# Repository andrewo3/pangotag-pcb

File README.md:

# Pangotag PCB

KiCad 10 project for a GNSS and motion tracking tag for the white-bellied pangolin, built in the
Harvard Microrobotics Laboratory.

## V2

`Pangotag_PCB_LCSC_compat4.kicad_pcb` is the V2 tag: a 31.94 × 27.18 mm, 6-layer, 1.6 mm board with
80 parts on both sides, using parts that JLCPCB stocks.

- STM32U575 microcontroller (LQFP-64) and a 32 GB eMMC on the underside
- u-blox MAX-M10S GNSS module with a U.FL antenna connector
- BMI270 IMU, BMP581 pressure sensor, T117 temperature sensor and LTC2944 coulomb counter on one I2C bus
- Two TPS62840 buck converters for always-on 1.9 V and 3.3 V rails, fed from a 2-pin battery connector
- USB-C for USB and, with a Type-C debug accessory, SWD: two comparators on CC1 and CC2 and an AND
  gate switch a TMUX1511 that puts SWCLK, SWDIO, SWO and NRST on contacts USB 2.0 leaves unused

`Dongle.kicad_pcb` is a 4-layer adapter that connects an ST-Link to the tag's USB-C port in either
orientation, with a reset button.

## Files

| Path | Contents |
| --- | --- |
| `Pangotag_PCB.kicad_sch` and its `Power`, `Communication`, `LEDs` and `st-link_conn` sheets | Schematic |
| `Pangotag_PCB_LCSC_compat4.kicad_pcb` | V2 tag board |
| `Dongle.kicad_pcb` | ST-Link debug dongle |
| `Pangotag_PCB.kicad_pcb` | The tag and an earlier dongle on one sheet |
| `Pangotag_PCB_LCSC_compat*.kicad_pcb`, `Only_Tag*.kicad_pcb` | Intermediate revisions |
| `jlcpcb/` | JLCPCB Gerber, BOM and placement files |
| `export_footprints.pretty/`, `FBGA153.pretty/`, `*.kicad_sym` | Project footprint and symbol libraries |
| `tag_render*.png` | Renders of the board and an enclosure model |

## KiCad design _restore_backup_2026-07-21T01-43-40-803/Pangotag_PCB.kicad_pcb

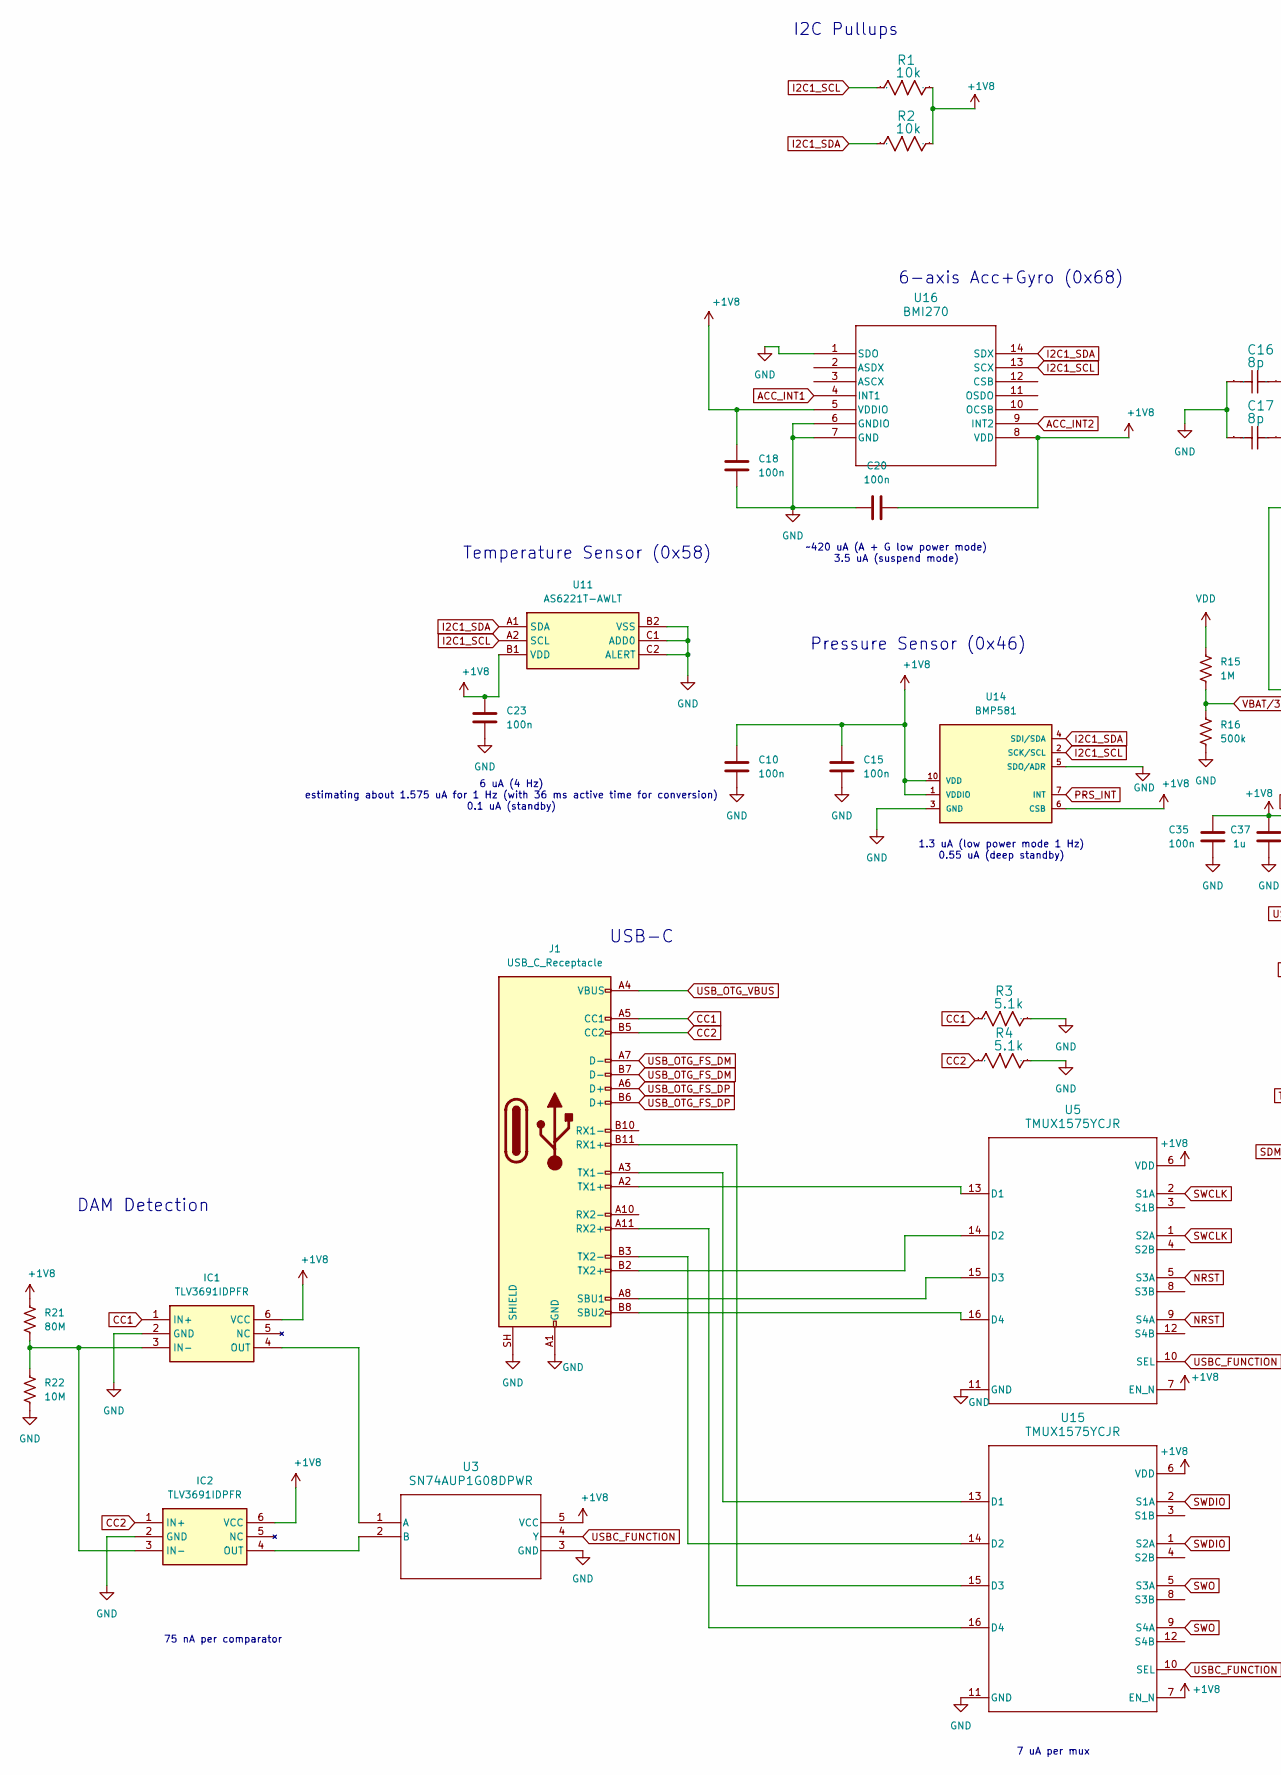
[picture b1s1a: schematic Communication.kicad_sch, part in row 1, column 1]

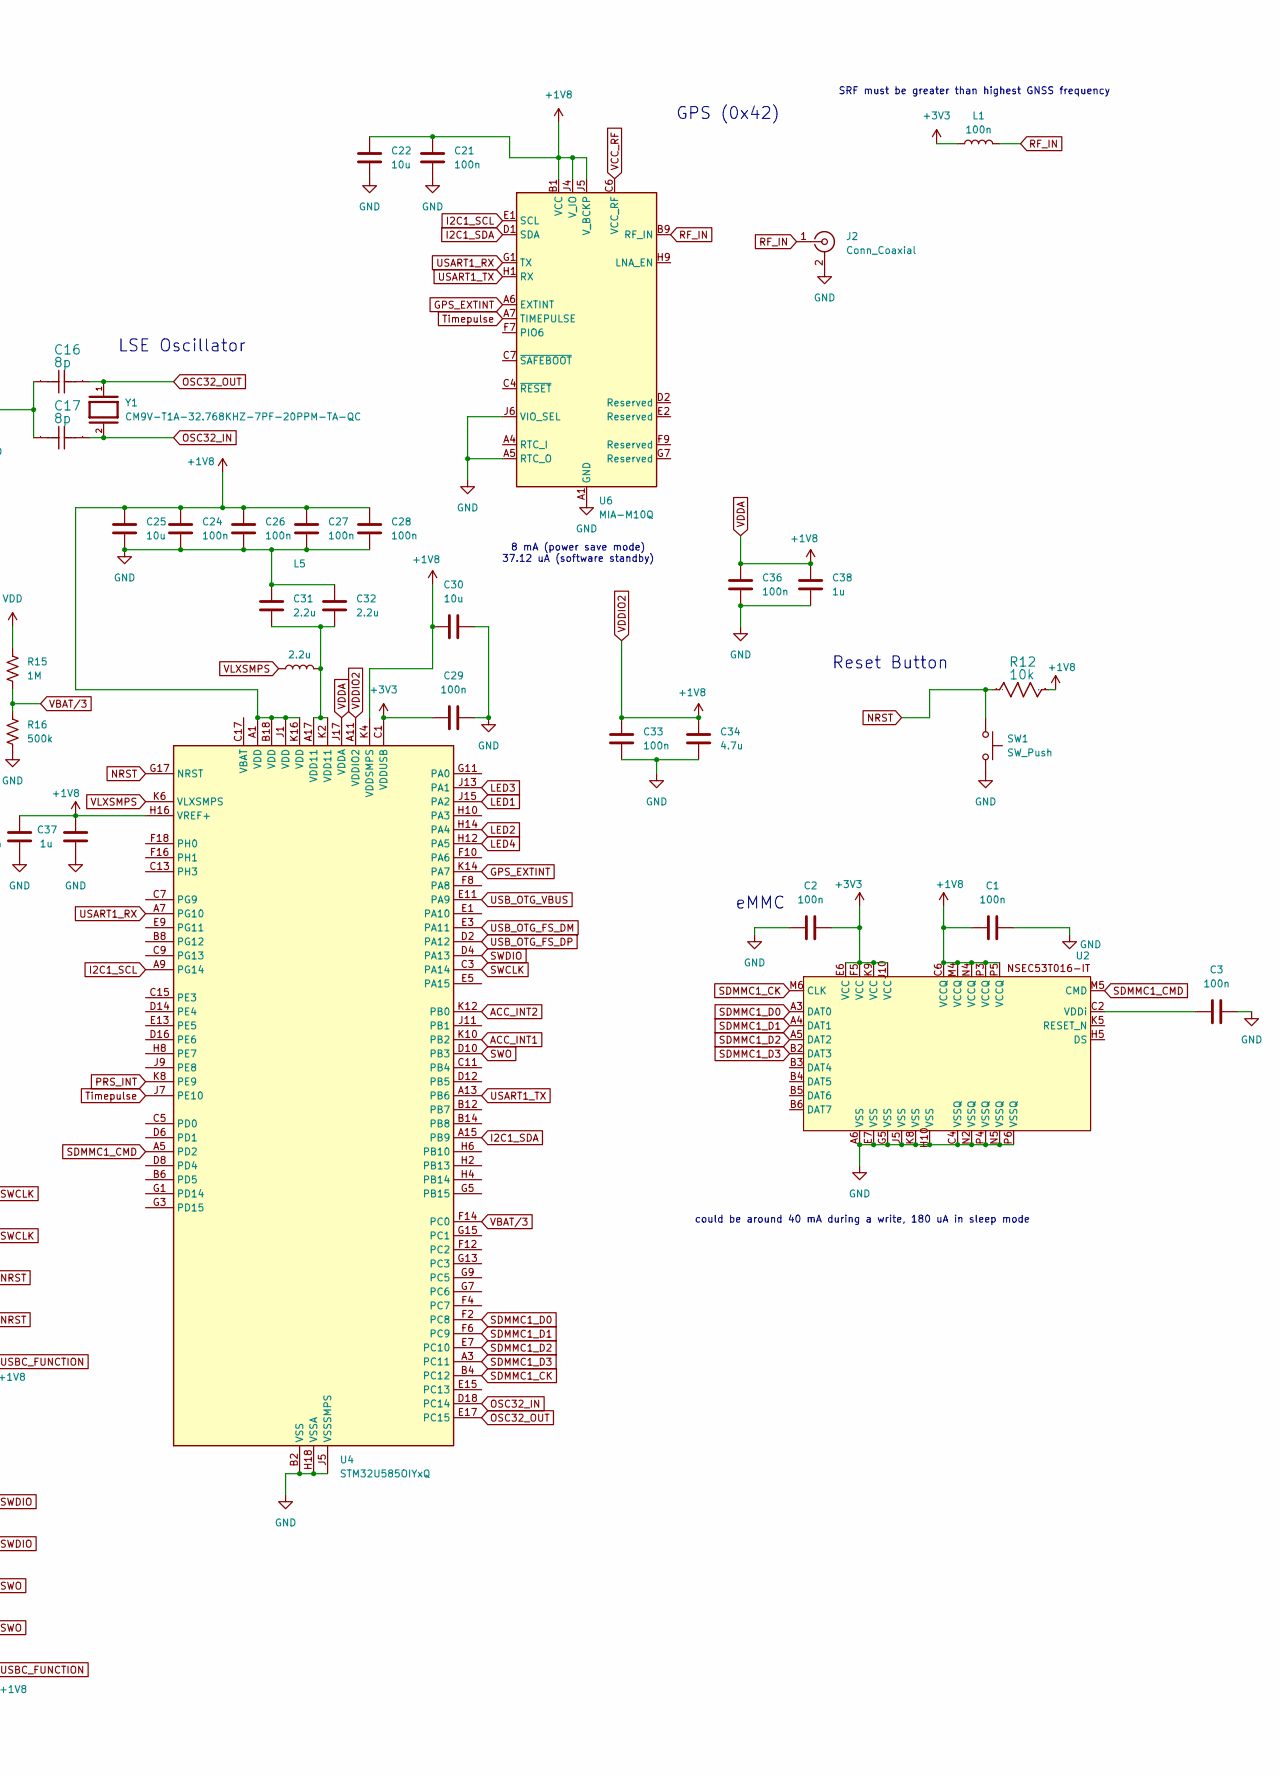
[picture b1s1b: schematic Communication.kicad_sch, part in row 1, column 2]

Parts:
C1, C2, C3, C10, C15, C18, C20, C21, C23, C24, C26, C27, C28, C29, C33, C35, C36: 100n; C_0201_0603Metric
C16, C17: 8p; C_0201_0603Metric
C22, C25, C30: 10u; C_0201_0603Metric
C31, C32: 2.2u; C_0201_0603Metric
C34: 4.7u; C_0201_0603Metric
C37, C38: 1u; C_0201_0603Metric
IC1, IC2: TLV3691IDPFR; Manufacturer_Part_Number TLV3691IDPFR; Mouser Part Number 595-TLV3691IDPFR
J1: USB_C_Receptacle; USB_C_Receptacle_Amphenol_12401610E4-2A_CircularHoles
J2: Conn_Coaxial; U.FL_Hirose_U.FL-R-SMT-1_Vertical
L1: 100n; L_0201_0603Metric
L5: 2.2u; L_0201_0603Metric
R1, R2, R12: 10k; R_0201_0603Metric
R3, R4: 5.1k; R_0201_0603Metric
R15: 1M; R_0201_0603Metric
R16: 500k; R_0201_0603Metric
R21: 80M; R_0201_0603Metric
R22: 10M; R_0201_0603Metric
SW1: SW_Push; SW_SPST_B3U-1000P
U2: BGA153N50P14X14_1150X1300X80
U3: SN74AUP1G08DPWR; DPW0005A_TEX
U4: STM32U585OIYxQ; ST_WLCSP-90_4.2x3.95mm_Layout18x10_P0.4mm_Stagger
U5, U15: TMUX1575YCJR; PREYCJ0016-IPC_A
U6: MIA-M10Q; ublox_LGA-53_4.5x4.5mm_Layout9x9_P0.5mm
U11: AS6221T-AWLT; BGA6C40P2X3_102X150X52; Manufacturer_Part_Number AS6221T-AWLT; Mouser Part Number 985-AS6221T-AWLT
U14: BMP581
U16: BMI270; BMI270_BOS
Y1: CM9V-T1A-32.768KHZ-7PF-20PPM-TA-QC; XTAL_CM9V-T1A-32.768KHZ-7PF-20PPM-TA-QC; PARTREV 8.2/07.2022

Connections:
+3V3: C2.2, C29.2, L1.1, U2.E6 (VCC), U2.F5 (VCC), U2.J10 (VCC), U2.K9 (VCC), U4.C1 (VDDUSB); also elsewhere on the board
ACC_INT1: U4.K10 (PB2), U16.4 (INT1)
ACC_INT2: U4.K12 (PB0), U16.9 (INT2)
CC1: IC1.1 (IN+), J1.A5 (CC1), R3.1
CC2: IC2.1 (IN+), J1.B5 (CC2), R4.1
GND: C1.2, C2.1, C3.2, C10.2, C15.2, C16.1, C17.1, C18.2, C20.1, C21.2, C22.2, C23.2, C24.1, C25.1, C26.1, C27.1, C28.1, C29.1, C30.1, C31.2, C32.2, C33.1, C34.1, C35.1, C36.1, C37.1, C38.1, IC1.2 (GND), IC2.2 (GND), J1.A1 (GND), J1.A12 (GND), J1.B1 (GND), J1.B12 (GND), J1.SH (SHIELD), J2.2 (Ext), R3.2, R4.2, R16.2, R22.2, SW1.2, U2.A6 (VSS), U2.C4 (VSSQ), U2.E7 (VSS), U2.G5 (VSS), U2.H10 (VSS), U2.J5 (VSS), U2.K8 (VSS), U2.N2 (VSSQ), U2.N5 (VSSQ), U2.P4 (VSSQ), U2.P6 (VSSQ), U3.3 (GND), U4.B2 (VSS), U4.B10 (VSS), U4.B16 (VSS), U4.H18 (VSSA), U4.J3 (VSS), U4.J5 (VSSSMPS), U4.K18 (VSS), U5.11 (GND), U6.A1 (GND), U6.A2 (GND), U6.A3 (GND), U6.A5 (RTC_O), U6.A8 (GND), U6.A9 (GND), U6.B2 (GND), U6.B8 (GND), U6.C3 (GND), U6.C9 (GND), U6.E3 (GND), U6.E4 (GND), U6.E9 (GND), U6.F1 (GND), U6.F3 (GND), U6.F4 (GND), U6.G3 (GND), U6.G4 (GND), U6.G5 (GND), U6.G6 (GND), U6.H8 (GND), U6.J6 (VIO_SEL), U6.J8 (GND), U6.J9 (GND), U11.B2 (VSS), U11.C1 (ADD0), U11.C2 (ALERT), U14.3 (GND), U14.5 (SDO/ADR), U14.8 (GND), U14.9 (GND), U15.11 (GND), U16.1 (SDO), U16.6 (GNDIO), U16.7 (GND); also elsewhere on the board
GPS_EXTINT: U4.K14 (PA7), U6.A6 (EXTINT)
I2C1_SCL: R1.1, U4.A9 (PG14), U6.E1 (SCL), U11.A2 (SCL), U14.2 (SCK/SCL), U16.13 (SCX); also elsewhere on the board
I2C1_SDA: R2.1, U4.A15 (PB9), U6.D1 (SDA), U11.A1 (SDA), U14.4 (SDI/SDA), U16.14 (SDX); also elsewhere on the board
LED1: U4.J15 (PA2); also elsewhere on the board
LED2: U4.H14 (PA4); also elsewhere on the board
LED3: U4.J13 (PA1); also elsewhere on the board
LED4: U4.H12 (PA5); also elsewhere on the board
NRST: R12.2, SW1.1, U4.G17 (NRST), U5.5 (S3A), U5.9 (S4A)
unnamed: C31.1, C32.1, L5.2, U4.A17 (VDD11), U4.K2 (VDD11)
unnamed: IC1.3 (IN-), IC2.3 (IN-), R21.2, R22.1
unnamed: IC1.4 (OUT), U3.1 (A)
unnamed: IC2.4 (OUT), U3.2 (B)
unnamed: J1.B11 (RX1+), U15.15 (D3)
unnamed: J1.A11 (RX2+), U15.16 (D4)
unnamed: J1.A8 (SBU1), U5.15 (D3)
unnamed: J1.B8 (SBU2), U5.16 (D4)
unnamed: J1.A2 (TX1+), U5.13 (D1)
unnamed: J1.A3 (TX1-), U15.13 (D1)
unnamed: J1.B2 (TX2+), U5.14 (D2)
unnamed: J1.B3 (TX2-), U15.14 (D2)
unnamed: C3.1, U2.C2 (VDDi)
OSC32_IN: C17.2, U4.D18 (PC14), Y1.2
OSC32_OUT: C16.2, U4.E17 (PC15), Y1.1
PRS_INT: U4.K8 (PE9), U14.7 (INT)
RF_IN: J2.1 (In), L1.2, U6.B9 (RF_IN)
SDMMC1_CK: U2.M6 (CLK), U4.B4 (PC12)
SDMMC1_CMD: U2.M5 (CMD), U4.A5 (PD2)
SDMMC1_D0: U2.A3 (DAT0), U4.F2 (PC8)
SDMMC1_D1: U2.A4 (DAT1), U4.F6 (PC9)
SDMMC1_D2: U2.A5 (DAT2), U4.E7 (PC10)
SDMMC1_D3: U2.B2 (DAT3), U4.A3 (PC11)
SWCLK: U4.C3 (PA14), U5.1 (S2A), U5.2 (S1A)
SWDIO: U4.D4 (PA13), U15.1 (S2A), U15.2 (S1A)
SWO: U4.D10 (PB3), U15.5 (S3A), U15.9 (S4A)
Timepulse: U4.J7 (PE10), U6.A7 (TIMEPULSE)
USART1_RX: U4.A7 (PG10), U6.G1 (TX)
USART1_TX: U4.A13 (PB6), U6.H1 (RX)
USBC_FUNCTION: U3.4 (Y), U5.10 (SEL), U15.10 (SEL)
USB_OTG_FS_DM: J1.A7 (D-), J1.B7 (D-), U4.E3 (PA11)
USB_OTG_FS_DP: J1.A6 (D+), J1.B6 (D+), U4.D2 (PA12)
USB_OTG_VBUS: J1.A4 (VBUS), J1.A9 (VBUS), J1.B4 (VBUS), J1.B9 (VBUS), U4.E11 (PA9)
VBAT/3: R15.2, R16.1, U4.F14 (PC0)
VCC_RF: U6.C6 (VCC_RF)
VDD: R15.1; also elsewhere on the board
VDDA: C1.1, C10.1, C15.1, C18.1, C20.2, C21.1, C22.1, C23.1, C24.2, C25.2, C26.2, C27.2, C28.2, C30.2, C33.2, C34.2, C35.2, C36.2, C37.2, C38.2, IC1.6 (VCC), IC2.6 (VCC), R1.2, R2.2, R12.1, R21.1, U2.C6 (VCCQ), U2.M4 (VCCQ), U2.N4 (VCCQ), U2.P3 (VCCQ), U2.P5 (VCCQ), U3.5 (VCC), U4.A1 (VDD), U4.A11 (VDDIO2), U4.B18 (VDD), U4.H16 (VREF+), U4.J1 (VDD), U4.J17 (VDDA), U4.K4 (VDDSMPS), U4.K16 (VDD), U5.6 (VDD), U5.7 (EN_N), U6.B1 (VCC), U6.J4 (V_IO), U6.J5 (V_BCKP), U11.B1 (VDD), U14.1 (VDDIO), U14.6 (CSB), U14.10 (VDD), U15.6 (VDD), U15.7 (EN_N), U16.5 (VDDIO), U16.8 (VDD); also elsewhere on the board
VLXSMPS: L5.1, U4.K6 (VLXSMPS)

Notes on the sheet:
Temperature Sensor (0x58)
GPS (0x42)
75 nA per comparator
I2C Pullups
SRF must be greater than highest GNSS frequency
Reset Button
8 mA (power save mode) 37.12 uA (software standby)
could be around 40 mA during a write, 180 uA in sleep mode
6-axis Acc+Gyro (0x68)
DAM Detection
eMMC
6 uA (4 Hz) estimating about 1.575 uA for 1 Hz (with 36 ms active time for conversion) 0.1 uA (standby)
7 uA per mux
1.3 uA (low power mode 1 Hz) 0.55 uA (deep standby)
LSE Oscillator
Pressure Sensor (0x46)
~420 uA (A + G low power mode) 3.5 uA (suspend mode)
USB-C

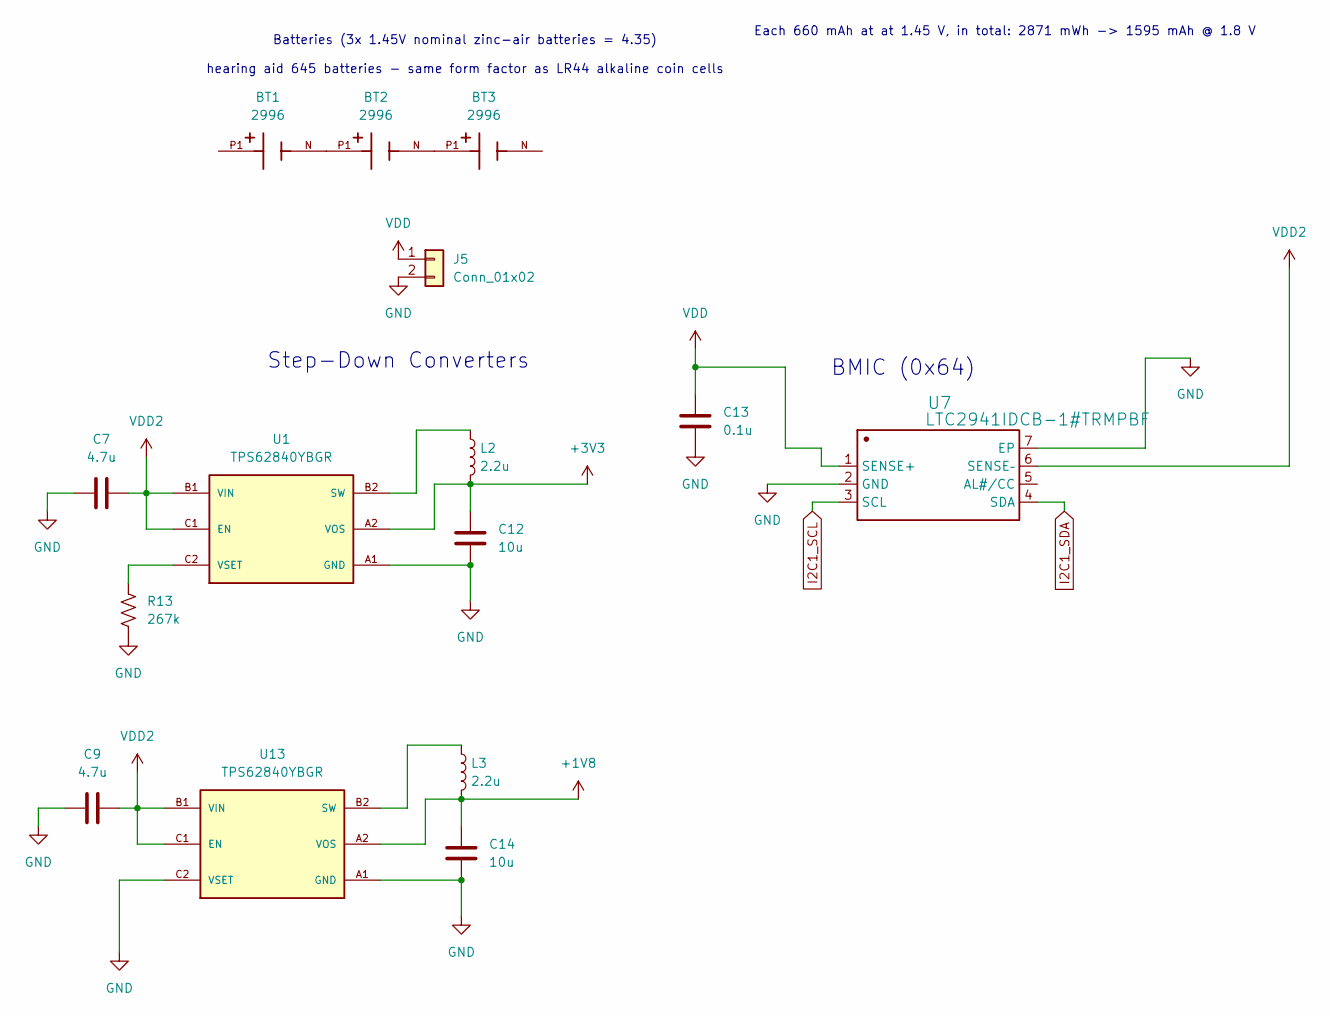
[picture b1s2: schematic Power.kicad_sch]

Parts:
BT1, BT2, BT3: 2996; BAT_2996; PARTREV F
C7, C9: 4.7u; C_0201_0603Metric
C12, C14: 10u; C_0201_0603Metric
C13: 0.1u; C_0201_0603Metric
J5: Conn_01x02; Hirose_DF57H-2P-1.2V_1x02_P1.2mm_Socket
L2, L3: 2.2u; L_0201_0603Metric
R13: 267k; R_0201_0603Metric
U1, U13: TPS62840YBGR; BGA6N40P3X2_146X96X50N; PARTREV D
U7: LTC2941IDCB-1#TRMPBF; DFN-6-1EP_3x2mm_P0.5mm_EP1.65x1.35mm; Manufacturer Part LTC2941IDCB-1#TRMPBF

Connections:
+3V3: C12.1, L2.2, U1.A2 (VOS); also elsewhere on the board
GND: C7.2, C9.2, C12.2, C13.2, C14.2, J5.2, R13.2, U1.A1 (GND), U7.2 (GND), U7.7 (EP), U13.A1 (GND), U13.C2 (VSET); also elsewhere on the board
I2C1_SCL: U7.3 (SCL); also elsewhere on the board
I2C1_SDA: U7.4 (SDA); also elsewhere on the board
unnamed: BT1.N, BT2.P1, BT2.P2
unnamed: BT1.P1, BT1.P2
unnamed: BT2.N, BT3.P1, BT3.P2
unnamed: L2.1, U1.B2 (SW)
unnamed: R13.1, U1.C2 (VSET)
unnamed: L3.1, U13.B2 (SW)
VDD: C13.1, J5.1, U7.1 (SENSE+); also elsewhere on the board
VDD2: C7.1, C9.1, U1.B1 (VIN), U1.C1 (EN), U7.6 (SENSE–), U13.B1 (VIN), U13.C1 (EN)
VDDA: C14.1, L3.2, U13.A2 (VOS); also elsewhere on the board

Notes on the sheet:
Each 660 mAh at at 1.45 V, in total: 2871 mWh -> 1595 mAh @ 1.8 V
BMIC (0x64)
Batteries (3x 1.45V nominal zinc-air batteries = 4.35) hearing aid 645 batteries - same form factor as LR44 alkaline coin cells
Step-Down Converters

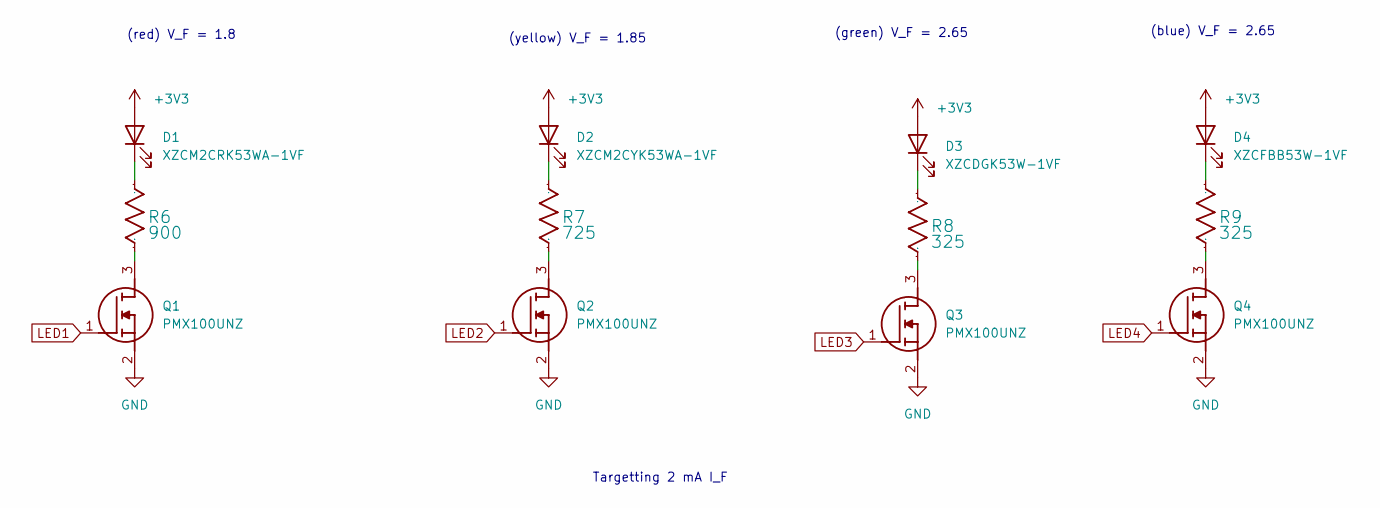
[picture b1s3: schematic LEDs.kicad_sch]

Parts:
D1: XZCM2CRK53WA-1VF; LED_0201_0603Metric
D2: XZCM2CYK53WA-1VF; LED_0201_0603Metric
D3: XZCDGK53W-1VF; LED_0201_0603Metric
D4: XZCFBB53W-1VF; LED_0201_0603Metric
Q1, Q2, Q3, Q4: PMX100UNZ; Manufacturer_Part_Number PMX100UNZ; Mouser Part Number 771-PMX100UNZ
R6: 900; R_0201_0603Metric
R7: 725; R_0201_0603Metric
R8, R9: 325; R_0201_0603Metric

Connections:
+3V3: D1.2 (A), D2.2 (A), D3.2 (A), D4.2 (A); also elsewhere on the board
GND: Q1.2 (S), Q2.2 (S), Q3.2 (S), Q4.2 (S); also elsewhere on the board
LED1: Q1.1 (G); also elsewhere on the board
LED2: Q2.1 (G); also elsewhere on the board
LED3: Q3.1 (G); also elsewhere on the board
LED4: Q4.1 (G); also elsewhere on the board
unnamed: D1.1 (K), R6.2
unnamed: D2.1 (K), R7.2
unnamed: D3.1 (K), R8.2
unnamed: D4.1 (K), R9.2
unnamed: Q1.3 (D), R6.1
unnamed: Q2.3 (D), R7.1
unnamed: Q3.3 (D), R8.1
unnamed: Q4.3 (D), R9.1

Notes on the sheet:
(blue) V_F = 2.65
(yellow) V_F = 1.85
(red) V_F = 1.8
(green) V_F = 2.65
Targetting 2 mA I_F

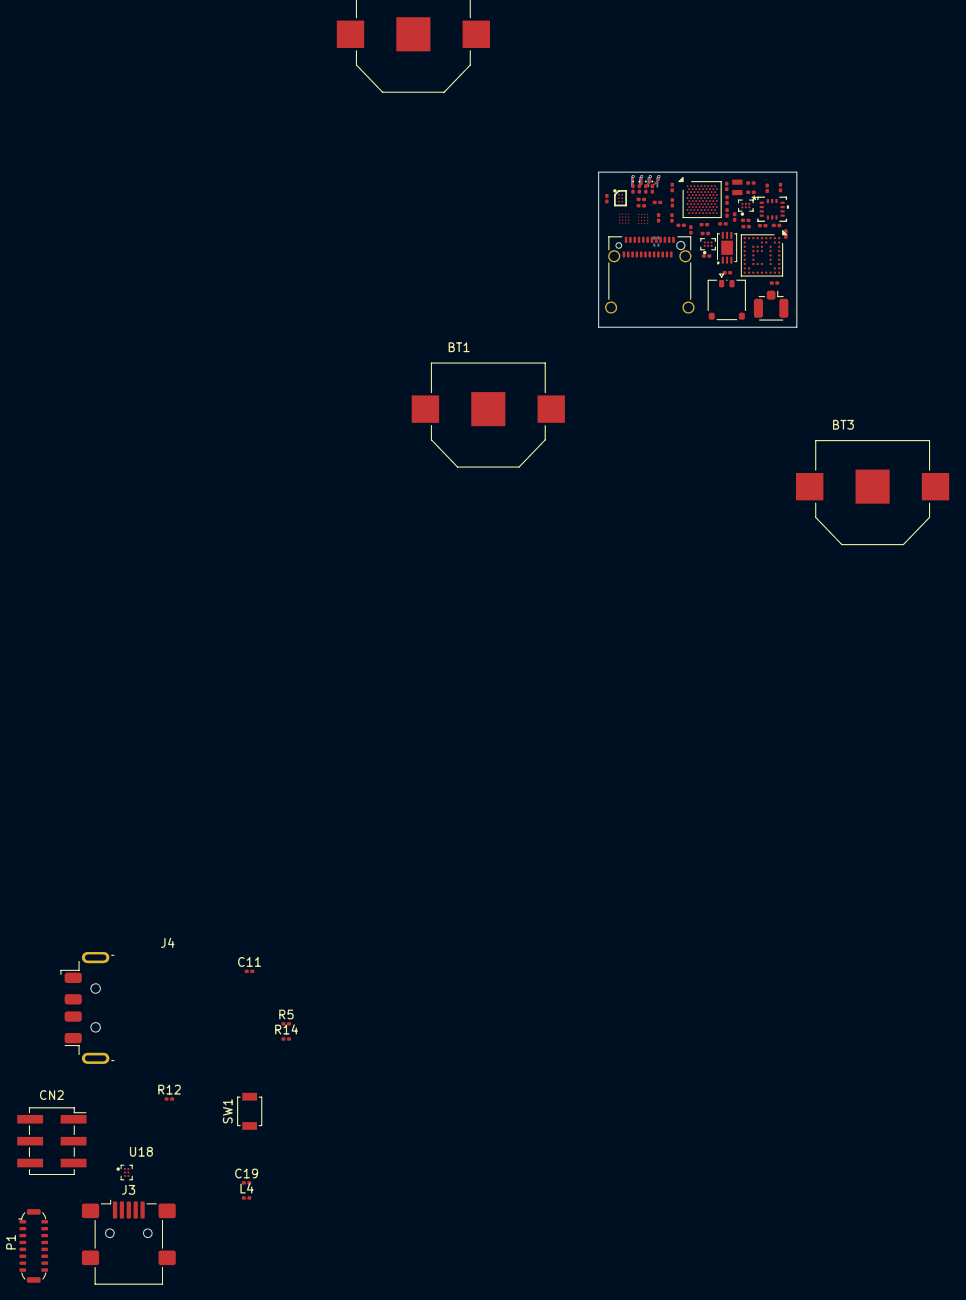
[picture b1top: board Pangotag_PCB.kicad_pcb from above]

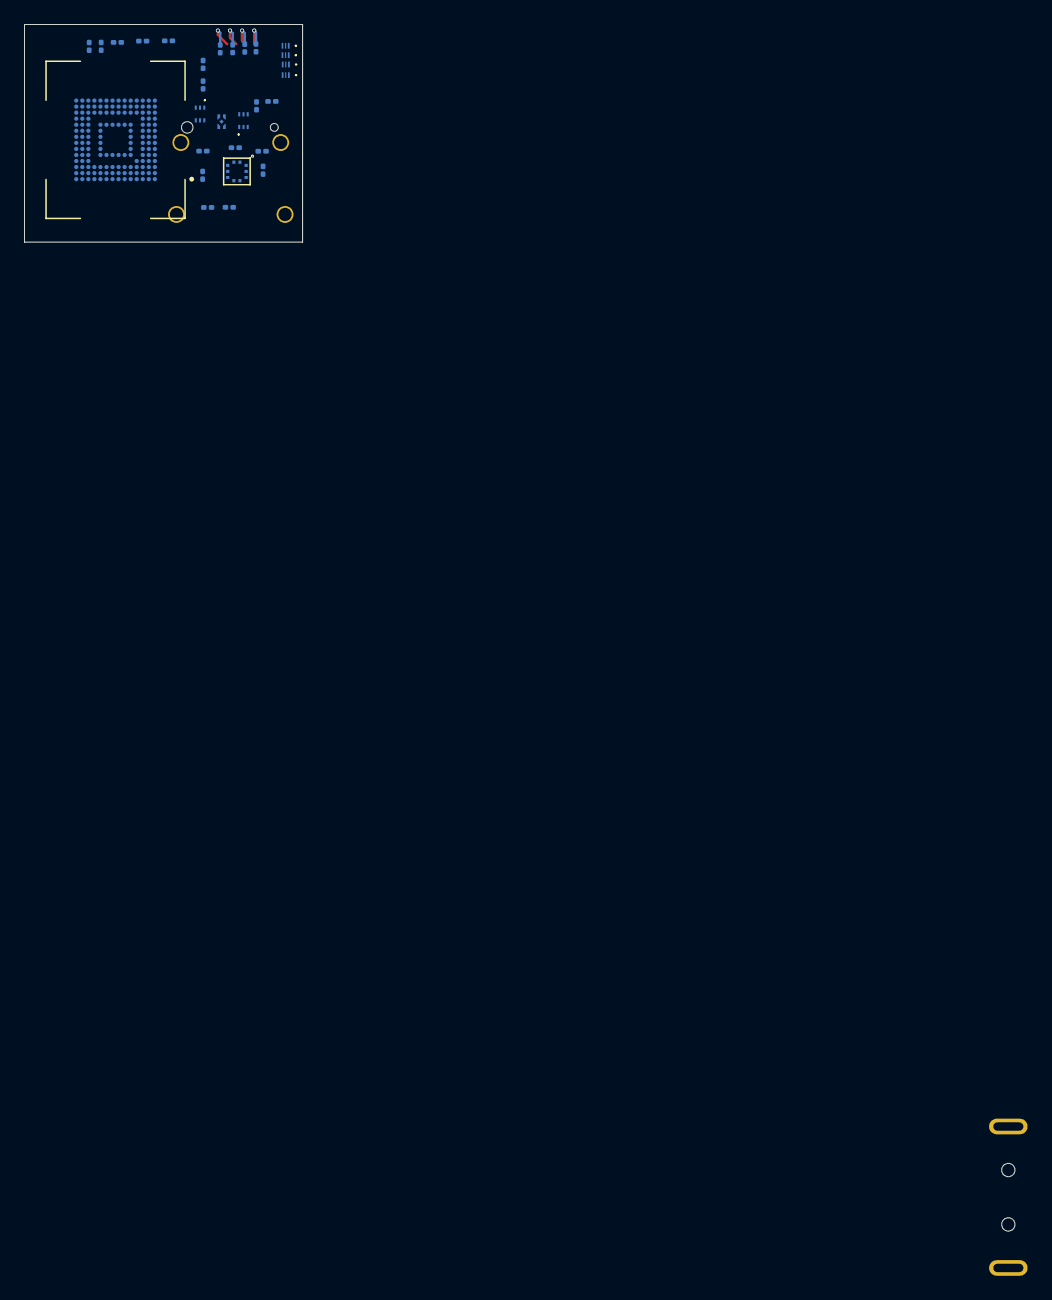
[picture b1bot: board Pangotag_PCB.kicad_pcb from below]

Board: 4 copper layers, 23.0 x 18.0 mm, 90 parts (29 on the bottom side), 74 nets.

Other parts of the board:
C11: 4.7u; C_0201_0603Metric
C19: 10u; C_0201_0603Metric
CN2: POGOPIN_2X04_P2.54_M; PinSocket_2x03_P2.54mm_Vertical_SMD
J3: USB_B_Mini; USB_Mini-B_Lumberg_2486_01_Horizontal
J4: USB_A; USB_A_Molex_48037-2200_Horizontal
L4: 2.2u; L_0201_0603Metric
P1: USB_C_Plug; USB_C_Plug_ShenzhenJingTuoJin_918-118A2021Y40002_Vertical
R5, R14: 56k; R_0201_0603Metric
U18: TPS62840YBGR; BGA6N40P3X2_146X96X50N

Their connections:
+1V8_2: C19.1, CN2.1, L4.2, U18.A2 (VOS)
GND: C11.2, C19.2, CN2.2, J3.5 (GND), J3.SH (Shield), J4.4 (GND), J4.SH (Shield), P1.A1 (GND), P1.A12 (GND), P1.B1 (GND), P1.B12 (GND), P1.SH (SHIELD), U18.A1 (GND), U18.C2 (VSET); also elsewhere on the board
NRST_OUT: CN2.6, P1.A8 (SBU1)
unnamed: J3.3 (D+), J4.3 (D+)
unnamed: J3.2 (D-), J4.2 (D-)
unnamed: P1.A5 (CC), R5.2
unnamed: P1.B5 (VCONN), R14.2
unnamed: L4.1, U18.B2 (SW)
VBUS_DONGLE: C11.1, J3.1 (VBUS), J4.1 (VBUS), P1.A4 (VBUS), P1.A9 (VBUS), P1.B4 (VBUS), P1.B9 (VBUS), R5.1, R14.1, U18.B1 (VIN), U18.C1 (EN)

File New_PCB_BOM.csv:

"Id";"Designator";"Footprint";"Quantity";"Designation";"Supplier and ref";
1;"BT1, BT2, BT3";"BAT_2996";3;"2996";;;
2;"C1, C2, C3, C10, C15, C18, C20, C21, C23, C29, C36, C37, C39, C40";"C_0201_0603Metric";14;"100n";;;
3;"C7, C8, C11";"C_0201_0603Metric";3;"4.7u";;;
4;"C13";"C_0201_0603Metric";1;"0.1u";;;
5;"C16, C17";"C_0201_0603Metric";2;"8p";;;
6;"C19, C22, C24, C25, C30, C35";"C_0201_0603Metric";6;"10u";;;
7;"C38";"C_0201_0603Metric";1;"1u";;;
8;"C41, C42";"C_0201_0603Metric";2;"2.2u";;;
9;"CN2";"PinSocket_2x03_P2.54mm_Vertical_SMD";1;"POGOPIN_2X04_P2.54_M";;;
10;"D1";"LED_0201_0603Metric";1;"XZCM2CRK53WA-1VF";;;
11;"D2";"LED_0201_0603Metric";1;"XZCM2CYK53WA-1VF";;;
12;"D3";"LED_0201_0603Metric";1;"XZCDGK53W-1VF";;;
13;"D4";"LED_0201_0603Metric";1;"XZCFBB53W-1VF";;;
14;"IC1, IC2";"TLV3691IDPFR";2;"TLV3691IDPFR";;;
15;"IC3, IC4";"SON50P150X200X100-8N-D";2;"TPS62840DLCR";;;
16;"IC5, IC6";"TS3A5018RSVR";2;"TS3A5018RSVR";;;
17;"J1";"USB_C_Receptacle_Amphenol_12401610E4-2A_CircularHoles";1;"USB_C_Receptacle";;;
18;"J2";"U.FL_Hirose_U.FL-R-SMT-1_Vertical";1;"Conn_Coaxial";;;
19;"J3";"USB_Mini-B_Lumberg_2486_01_Horizontal";1;"USB_B_Mini";;;
20;"J4";"USB_A_Molex_48037-2200_Horizontal";1;"USB_A";;;
21;"J5";"Hirose_DF57H-2P-1.2V_1x02_P1.2mm_Socket";1;"Conn_01x02";;;
22;"L1";"L_0201_0603Metric";1;"100n";;;
23;"L4, L5, L6, L7";"L_0201_0603Metric";4;"2.2u";;;
24;"P1";"USB_C_Plug_ShenzhenJingTuoJin_918-118A2021Y40002_Vertical";1;"USB_C_Plug";;;
25;"Q1, Q2, Q3, Q4";"PMX100UNZ";4;"PMX100UNZ";;;
26;"R1, R2, R12";"R_0201_0603Metric";3;"10k";;;
27;"R3, R4";"R_0201_0603Metric";2;"5.1k";;;
28;"R5, R14";"R_0201_0603Metric";2;"56k";;;
29;"R6";"R_0201_0603Metric";1;"900";;;
30;"R7";"R_0201_0603Metric";1;"725";;;
31;"R8, R9";"R_0201_0603Metric";2;"325";;;
32;"R13";"R_0201_0603Metric";1;"267k";;;
33;"R15";"R_0201_0603Metric";1;"1M";;;
34;"R16";"R_0201_0603Metric";1;"500k";;;
35;"R21";"R_0201_0603Metric";1;"80M";;;
36;"R22";"R_0201_0603Metric";1;"10M";;;
37;"SW1";"SW_SPST_B3U-1000P";1;"SW_Push";;;
38;"U2";"BGA153N50P14X14_1150X1300X80";1;"~";;;
39;"U3";"DPW0005A_TEX";1;"SN74AUP1G08DPWR";;;
40;"U4";"ublox_MAX";1;"MAX-M10S";;;
41;"U7";"DFN-6-1EP_3x2mm_P0.5mm_EP1.65x1.35mm";1;"LTC2941IDCB-1#TRMPBF";;;
42;"U8";"LQFP-64_10x10mm_P0.5mm";1;"STM32U585RITxQ";;;
43;"U11";"BGA6C40P2X3_102X150X52";1;"AS6221T-AWLT";;;
44;"U14";"BMP581";1;"BMP581";;;
45;"U16";"BMI270_BOS";1;"BMI270";;;
46;"U18";"BGA6N40P3X2_146X96X50N";1;"TPS62840YBGR";;;
47;"Y1";"XTAL_CM9V-T1A-32.768KHZ-7PF-20PPM-TA-QC";1;"CM9V-T1A-32.768KHZ-7PF-20PPM-TA-QC";;;

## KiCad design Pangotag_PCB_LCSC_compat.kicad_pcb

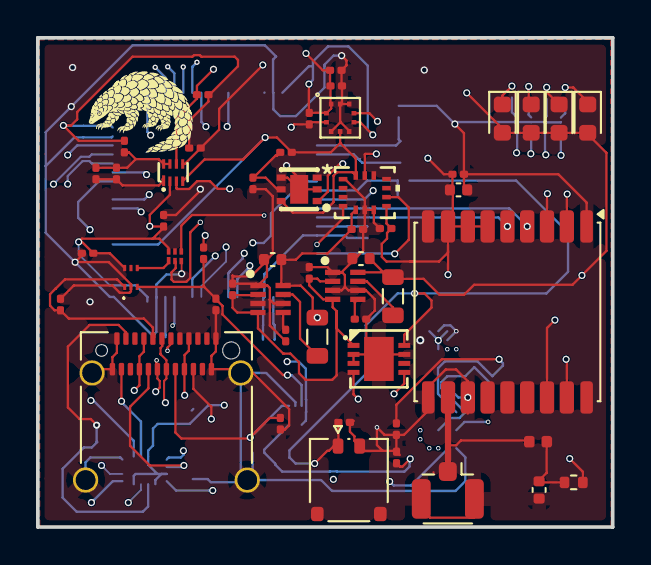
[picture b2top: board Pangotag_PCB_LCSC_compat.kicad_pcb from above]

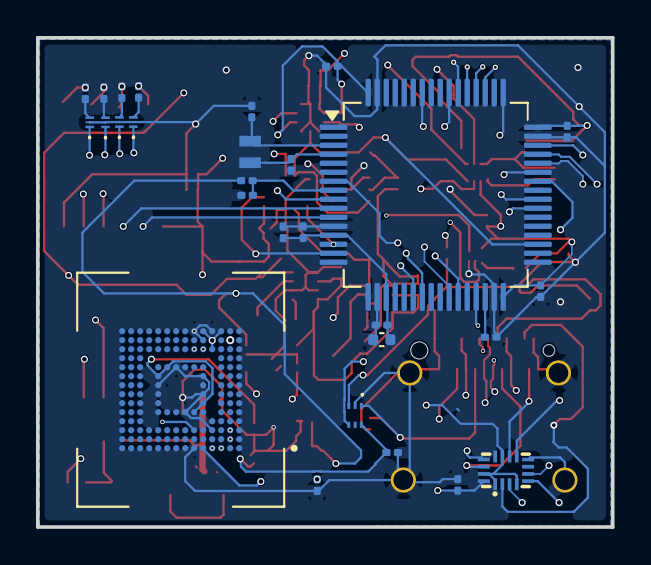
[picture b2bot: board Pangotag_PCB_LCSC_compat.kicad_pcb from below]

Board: 6 copper layers, 31.9 x 27.2 mm, 79 parts (28 on the bottom side), 63 nets.

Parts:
C1, C2, C3, C10, C14, C15, C18, C20, C21, C23, C26, C27, C28, C29, C31, C36, C37, C39, C40: 100n; C_0201_0603Metric
C4: 10n; C_0402_1005Metric
C7, C8, C33: 4.7u; C_0201_0603Metric
C13: 0.1u; C_0201_0603Metric
C16, C17: 8p; C_0201_0603Metric
C22, C24, C25, C35: 10u; C_0402_1005Metric
C30: 100p; C_0201_0603Metric
C38: 1u; C_0201_0603Metric
D1: XZCM2CRK53WA-1VF; LED_0603_1608Metric
D2: XZCM2CYK53WA-1VF; LED_0603_1608Metric
D3: XZCDGK53W-1VF; LED_0603_1608Metric
D4: XZCFBB53W-1VF; LED_0603_1608Metric
IC1, IC2: TLV3691IDPFR
IC3, IC4: TPS62840DLCR; SON50P150X200X100-8N-D
J1: USB_C_Receptacle; USB_C_Receptacle_Amphenol_12401610E4-2A_CircularHoles
J2: Conn_Coaxial; U.FL_Hirose_U.FL-R-SMT-1_Vertical
J5: Conn_01x02; Hirose_DF57H-2P-1.2V_1x02_P1.2mm_Socket
L1: 27n; L_0402_1005Metric
L5, L7: 2.2u; L_0805_2012Metric
Q1, Q2, Q3, Q4: PMX100UNZ
R1, R2, R19, R20: 10k; R_0201_0603Metric
R3, R4: 5.1k; R_0201_0603Metric
R5: 10; R_0402_1005Metric
R6: 900; R_0201_0603Metric
R7: 725; R_0201_0603Metric
R8, R9: 325; R_0201_0603Metric
R13: 267k; R_0201_0603Metric
R14: 909; R_0201_0603Metric
R15: 1M; R_0201_0603Metric
R16: 500k; R_0201_0603Metric
R18: 200k; R_0201_0603Metric
R21: 80M; R_0201_0603Metric
R22: 10M; R_0201_0603Metric
U1: 74AUP1G08GS_132; XSON6_SOT1202_NEX
U2: NSEC53T016T; BGA153N50P14X14_1150X1300X80
U3: T117_C19284874; TDFN-6_L2.0-W2.0-P0.65-TL-EP
U4: MAX-M10S; ublox_MAX
U5: STM32U575RGTx; LQFP-64_10x10mm_P0.5mm
U6: LTC2944IDD#PBF; DFN-8_L3.0-W3.0-P0.50-BL-EP
U7: TMUX1511RSVR; UTQFN-16_L2.6-W1.8-P0.40-BL
U8: PCA9306DQER; X2SON-8_L1.4-W1.0-P0.35-BL
U14: BMP581
U16: BMI270; BMI270_BOS
Y1: CM9V-T1A-32.768KHZ-7PF-20PPM-TA-QC; XTAL_CM9V-T1A-32.768KHZ-7PF-20PPM-TA-QC

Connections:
+3V3: C2.2, C24.1, C29.2, D1.2 (A), D2.2 (A), D3.2 (A), D4.2 (A), IC3.8 (VOS), L5.1, R5.1, R18.1, R19.1, R20.1, U2.E6 (VCC), U2.F5 (VCC), U2.J10 (VCC), U2.K9 (VCC), U5.48 (VDDUSB)
ACC_INT1: U5.14 (PA0), U16.4 (INT1)
ACC_INT2: U5.15 (PA1), U16.9 (INT2)
CC1: IC1.1 (IN+), J1.A5 (CC1), R3.1
CC2: IC2.1 (IN+), J1.B5 (CC2), R4.1
GND: C1.2, C2.1, C3.2, C4.2, C7.2, C8.2, C10.2, C13.2, C14.2, C15.2, C16.1, C17.1, C18.2, C20.1, C21.2, C22.2, C23.2, C24.2, C25.2, C26.2, C27.2, C28.2, C29.1, C30.2, C31.2, C33.2, C35.1, C36.1, C37.1, C38.1, C39.1, C40.1, IC1.2 (GND), IC2.2 (GND), IC3.1 (GND), IC3.3 (MODE), IC3.6 (STOP), IC4.1 (GND), IC4.3 (MODE), IC4.6 (STOP), J1.A1 (GND), J1.A12 (GND), J1.B1 (GND), J1.B12 (GND), J1.SH (SHIELD), J2.2 (Ext), J5.2, Q1.2 (S), Q2.2 (S), Q3.2 (S), Q4.2 (S), R3.2, R4.2, R13.2, R14.2, R16.2, R22.2, U1.3 (GND), U2.A6 (VSS), U2.C4 (VSSQ), U2.E7 (VSS), U2.G5 (VSS), U2.H10 (VSS), U2.J5 (VSS), U2.K8 (VSS), U2.N2 (VSSQ), U2.N5 (VSSQ), U2.P4 (VSSQ), U2.P6 (VSSQ), U3.2 (GND), U3.4 (ADDR), U3.7 (EP), U4.1 (GND), U4.10 (GND), U4.12 (GND), U5.12 (VSSA), U5.18 (VSS), U5.31 (VSS), U5.47 (VSS), U5.63 (VSS), U6.2 (GND), U6.3 (GND), U6.7 (GND), U6.9 (EP), U7.8 (GND), U8.1 (GND), U14.3 (GND), U14.5 (SDO/ADR), U14.8 (GND), U14.9 (GND), U16.1 (SDO), U16.6 (GNDIO), U16.7 (GND)
GPS_EXTINT: U4.5 (EXTINT), U5.11 (PC3)
I2C1_SCL: R1.1, U3.1 (SCL), U4.17 (SCL), U5.29 (PB10), U8.3 (SCL1), U14.2 (SCK/SCL), U16.13 (SCX)
I2C1_SCL_3V3: R19.2, U6.4 (SCL), U8.6 (SCL2)
I2C1_SDA: R2.1, U3.6 (SDA), U4.16 (SDA), U5.35 (PB14), U8.4 (SDA1), U14.4 (SDI/SDA), U16.14 (SDX)
I2C1_SDA_3V3: R20.2, U6.5 (SDA), U8.5 (SDA2)
LED1: Q1.1 (G), U5.27 (PB1)
LED2: Q2.1 (G), U5.26 (PB0)
LED3: Q3.1 (G), U5.23 (PA7)
LED4: Q4.1 (G), U5.22 (PA6)
NRST: U5.7 (NRST), U7.13 (D4)
unnamed: C4.1, L1.1, R5.2
unnamed: D1.1 (K), R6.2
unnamed: D2.1 (K), R7.2
unnamed: D3.1 (K), R8.2
unnamed: D4.1 (K), R9.2
unnamed: IC1.3 (IN-), IC2.3 (IN-), R21.2, R22.1
unnamed: IC1.4 (OUT), U1.1 (B)
unnamed: IC2.4 (OUT), U1.2 (A)
unnamed: IC3.7 (SW), L5.2
unnamed: IC3.5 (VSET), R13.1
unnamed: IC4.7 (SW), L7.2
unnamed: IC4.5 (VSET), R14.1
unnamed: J1.B11 (RX1+), U7.10 (S3)
unnamed: J1.B8 (SBU2), U7.14 (S4)
unnamed: J1.A2 (TX1+), U7.2 (S1)
unnamed: J1.B3 (TX2-), U7.5 (S2)
unnamed: Q1.3 (D), R6.1
unnamed: Q2.3 (D), R7.1
unnamed: Q3.3 (D), R8.1
unnamed: Q4.3 (D), R9.1
unnamed: C3.1, U2.C2 (VDDi)
unnamed: C33.1, U5.30 (VCAP)
unnamed: C14.1, C30.1, R18.2, U8.7 (VREF2), U8.8 (EN)
OSC32_IN: C17.2, U5.3 (PC14), Y1.2
OSC32_OUT: C16.2, U5.4 (PC15), Y1.1
PRS_INT: U5.9 (PC1), U14.7 (INT)
RF_IN: J2.1 (In), L1.2, U4.11 (RF_IN)
SDMMC1_CK: U2.M6 (CLK), U5.53 (PC12)
SDMMC1_CMD: U2.M5 (CMD), U5.54 (PD2)
SDMMC1_D0: U2.A3 (DAT0), U5.39 (PC8)
SDMMC1_D1: U2.A4 (DAT1), U5.40 (PC9)
SDMMC1_D2: U2.A5 (DAT2), U5.51 (PC10)
SDMMC1_D3: U2.B2 (DAT3), U5.52 (PC11)
SWCLK: U5.49 (PA14), U7.3 (D1)
SWDIO: U5.46 (PA13), U7.6 (D2)
SWO: U5.55 (PB3), U7.9 (D3)
Timepulse: U4.4 (TIMEPULSE), U5.10 (PC2)
USART1_RX: U4.2 (TXD), U5.43 (PA10)
USART1_TX: U4.3 (RXD), U5.58 (PB6)
USBC_FUNCTION: U1.4 (Y), U7.1 (SEL1), U7.4 (SEL2), U7.11 (SEL3), U7.15 (SEL4)
USB_OTG_FS_D+: J1.A6 (D+), J1.B6 (D+), U5.45 (PA12)
USB_OTG_FS_D-: J1.A7 (D-), J1.B7 (D-), U5.44 (PA11)
USB_OTG_VBUS: J1.A4 (VBUS), J1.A9 (VBUS), J1.B4 (VBUS), J1.B9 (VBUS), U5.42 (PA9)
VBAT/3: R15.2, R16.1, U5.8 (PC0)
VDD: C13.1, J5.1, R15.1, U6.8 (SENSE–)
VDD2: C7.1, C8.1, IC3.2 (VIN), IC3.4 (EN), IC4.2 (VIN), IC4.4 (EN), U6.1 (SENSE+)
VDDA: C1.1, C10.1, C15.1, C18.1, C20.2, C21.1, C22.1, C23.1, C25.1, C26.1, C27.1, C28.1, C31.1, C35.2, C36.2, C37.2, C38.2, C39.2, C40.2, IC1.6 (VCC), IC2.6 (VCC), IC4.8 (VOS), L7.1, R1.2, R2.2, R21.1, U1.6 (VCC), U2.C6 (VCCQ), U2.M4 (VCCQ), U2.N4 (VCCQ), U2.P3 (VCCQ), U2.P5 (VCCQ), U3.5 (VDD), U4.6 (V_BCKP), U4.7 (VCC_IO), U4.8 (VCC), U5.13 (VDDA), U5.19 (VDD), U5.32 (VDD), U5.64 (VDD), U7.16 (VDD), U8.2 (VREF1), U14.1 (VDDIO), U14.6 (CSB), U14.10 (VDD), U16.5 (VDDIO), U16.8 (VDD)

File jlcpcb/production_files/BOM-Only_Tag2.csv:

Comment,Designator,Footprint,LCSC,Quantity
0.1u,C13,C_0201_0603Metric,C66938,1
10,R5,R_0402_1005Metric,C25077,1
100n,"C1,C10,C15,C18,C2,C20,C21,C23,C26,C27,C28,C29,C3,C31,C32,C36,C37,C39,C40",C_0201_0603Metric,C66938,19
10M,R22,R_0201_0603Metric,C470889,1
10k,"R1,R2",R_0201_0603Metric,C98098,2
10n,C4,C_0402_1005Metric,C1524,1
10u,"C22,C24,C25,C30,C35",C_0402_1005Metric,C15525,5
1M,R15,R_0201_0603Metric,C102686,1
1u,C38,C_0201_0603Metric,C53067,1
2.2u,"C41,C42",C_0201_0603Metric,C77762,2
2.2u,"L5,L6,L7",L_0805_2012Metric,C98033,3
267k,R13,R_0201_0603Metric,C423627,1
27n,L1,L_0402_1005Metric,C12669,1
325,"R8,R9",R_0201_0603Metric,C100175,2
4.7u,"C7,C8",C_0201_0603Metric,C335103,2
5.1k,"R3,R4",R_0201_0603Metric,C163490,2
500k,R16,R_0201_0603Metric,C158436,1
725,R7,R_0201_0603Metric,C138124,1
80M,R21,R_0201_0603Metric,C423539,1
8p,"C16,C17",C_0201_0603Metric,C85917,2
900,R6,R_0201_0603Metric,C158303,1
BMI270,U16,BMI270_BOS,C2836813,1
BMP581,U14,BMP581,C5362283,1
CM9V-T1A-32.768KHZ-7PF-20PPM-TA-QC,Y1,XTAL_CM9V-T1A-32.768KHZ-7PF-20PPM-TA-QC,C5341288,1
Conn_01x02,J5,Hirose_DF57H-2P-1.2V_1x02_P1.2mm_Socket,C202104,1
Conn_Coaxial,J2,U.FL_Hirose_U.FL-R-SMT-1_Vertical,C88373,1
MAX-M10S,U4,ublox_MAX,C4153167,1
PMX100UNZ,"Q1,Q2,Q3,Q4",PMX100UNZ,C20235855,4
SN74AUP1G08DPWR,U3,DPW0005A_TEX,C2872914,1
STM32U585RITxQ,U8,LQFP-64_10x10mm_P0.5mm,C5271044,1
TLV3691IDPFR,"IC1,IC2",TLV3691IDPFR,C140305,2
TPS62840DLCR,"IC3,IC4",SON50P150X200X100-8N-D,C2071859,2
USB_C_Receptacle,J1,USB_C_Receptacle_Amphenol_12401610E4-2A_CircularHoles,C464604,1
XZCDGK53W-1VF,D3,LED_0603_1608Metric,C598356,1
XZCFBB53W-1VF,D4,LED_0603_1608Metric,C5200747,1
XZCM2CRK53WA-1VF,D1,LED_0603_1608Metric,C241893,1
XZCM2CYK53WA-1VF,D2,LED_0603_1608Metric,C2900143,1
AS6221T-AWLT,U11,BGA6C40P2X3_102X150X52,,1
LTC2941IDCB-1#TRMPBF,U7,DFN-6-1EP_3x2mm_P0.5mm_EP1.65x1.35mm,,1
NSEC3T016-IT,U2,BGA153N50P14X14_1150X1300X80,,1
